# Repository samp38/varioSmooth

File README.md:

# VarioSmooth

Lightweight, solar powered, helmet embedded audio variometer for free flight.

- [**v1**](v1/README.md) (2017): PIC24F16KA101 + MS5611, LTC4071 solar charger, 22 × 17 mm PCB. Firmware (MPLAB X / XC16), PCB (Eagle, ported to KiCad 10), docs and open issues.
- [**v2**](v2/README.md) (in progress): nRF52840 (Raytac MDBT50Q) with Bluetooth LE, sends barometric altitude and vario to XCTrack / LK8000. Firmware with PlatformIO, flex PCB.

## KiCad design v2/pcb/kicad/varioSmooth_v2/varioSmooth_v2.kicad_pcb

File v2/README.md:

# VarioSmooth v2 — BLE

Notes de conception pour la modernisation du vario (2026-10).

## Objectifs
- MCU **nRF52840** avec BLE : paramétrage depuis le téléphone + envoi de la pression et du vario à **XCTrack** (puis LK8000) sur Android.
- **Vario sans GPS** : l'application utilise le GPS du téléphone.
- Schéma sous **KiCad**, carte redessinée pour l'intégration dans le casque.
- Firmware compilé/flashé avec **PlatformIO**.
- **Contrainte n°1 : la consommation.**

## Réorientation : deux appareils (2026-10-20, redéfinie le 2026-10-22)
La v1 marche, mais elle est pénible à installer : les fils passés par l'aération cassent, la carte est trop épaisse pour la doublure, et le flashage au PICkit est laborieux. Le projet est scindé en deux appareils :

| | **Vario casque** | **Extension** (cockpit) |
|---|---|---|
| Rôle | Bip + pression et vario (`$LK8EX1`) vers XCTrack : le baro du vario donne une finesse calculée correcte | **Batterie externe** du téléphone + vario (bip activable) + **logger GPS IGC** + BLE |
| Intégration | Dans le casque, cellules solaires sur le dessus, comme la v1 | Boîtier dans le cockpit ou la sellette |
| MCU | nRF52840 (MDBT50Q, ou ISP1807 pour gagner de la place) | nRF52840 |
| USB | **Aucun** : SWD une seule fois, puis OTA BLE | USB-C : recharge, flash, récupération du log |
| Énergie | LiPo + 2 × SP3-12 + LTC4071, comme la v1 | Li-ion **18650** + panneau solaire (prolonge un peu l'autonomie) |
| Interface | Un bouton | Boutons **+ / − / push**, petit écran, menu |

### Vario casque
- **Pas de connecteur USB** (il serait inaccessible) : J1, U1 (protection ESD), R2, R3, R4, D2 et C4 disparaissent. Carte routée avec le MDBT50Q : **20 × 25,25 mm** (~15 × 18 mm estimés avec un ISP1807).
- **Module : à trancher** entre le MDBT50Q et l'**Insight SiP ISP1807** (même nRF52840, donc même firmware) :

  | | MDBT50Q-1MV2 | ISP1807 |
  |---|---|---|
  | Taille | 10,5 × 15,5 × 2,05 mm + zone d'antenne | 8 × 8 × 1 mm, antenne intégrée |
  | Quartz | 32 MHz intégré, 32,768 kHz externe (Y1, C5, C6) | 32 MHz et 32,768 kHz a priori intégrés (à vérifier) |
  | Prix | ~10 € | ~15–20 € (stock à vérifier) |
  | Soudure | Pads accessibles, air chaud possible | LGA à pas fin : pochoir + four |
  | Bootloader | Déjà présent sur un module récupéré d'une Feather | Rien : sonde SWD obligatoire |
  | Carte Adafruit | Définition Feather nRF52840 utilisable telle quelle | Pas de variante : définition de carte à adapter |

  Dans les deux cas, l'antenne doit être au bord de la carte, avec une zone sans cuivre.
- **Flash** : bootloader Adafruit flashé une fois par SWD (sonde CMSIS-DAP), puis mises à jour en **OTA BLE** (nRF Connect ou Bluefruit). Le bouton reste sur **P1.02** : maintenu à la mise sous tension, il lance le bootloader en mode DFU, ce qui permet de récupérer un firmware planté sans ouvrir le casque.
- **Pastilles de test** au dos (Ø 1,5 mm, pas de 2,54 mm, pour pogo pins) : 3V3, GND, RESET, SWDIO, SWDCLK.
- **Reset sans bouton** : la batterie est soudée, on ne peut pas la débrancher pour relancer le nRF. Les pastilles RESET et GND sont voisines : les toucher ensemble avec une pince fait un reset. Un bouton, même petit, dépasserait et risquerait des resets intempestifs dans la doublure. Reset avec P1.02 maintenu (ou double reset) → DFU, pour reflasher une appli plantée ou une OTA ratée. Un bootloader corrompu ne se répare que par SWD.
- **Buzzer sur la carte** : à tester avant de l'adopter. Un piézo CMS (~9 × 9 mm, résonance ~4 kHz) est bien plus faible qu'un KPEG006 aux fréquences du vario (400–1500 Hz) ; il ne convient que si la carte est près de l'oreille. Essai : Feather + piézo CMS contre KPEG006, casque sur la tête, avec un ventilateur.
- **Fils vers les cellules** : point faible de la v1, prévoir un passage propre et un serre-câble collé sur la carte.
- La version avec USB-C (20 × 32,75 mm, commit `d064723`) reste disponible dans l'historique git comme **prototype de développement**.

### Extension : batterie externe, vario et logger
- **Batterie** : 18650 en **1S** (1 ou 2 cellules en parallèle, ~3000–3500 mAh chacune) : pas d'équilibrage, chargeurs et élévateurs courants. 2 cellules : ~37 × 65 × 19 mm, ~95 g. Cellules de marque (Samsung 35E, Molicel, LG).
- **Alimentation** : chargeur type **TI BQ25895** (le LTC4071 ne convient plus) :
  - power path (l'appareil fonctionne pendant la charge) ;
  - sortie 5 V élevée (OTG, ~2–3 A) pour le téléphone ;
  - NTC avec seuils JEITA : pas de charge sous 0 °C ;
  - régulation de la tension d'entrée (VINDPM), qui fait office de MPPT simplifié pour un panneau de 6 V nominal ;
  - suivi par I²C depuis le nRF (niveau, courants, état).
  - Alternative écartée : IP5328P (charge rapide PD/QC intégrée, mais peu documenté et peu pilotable).
- **Connectique** : USB-C en entrée ; sortie USB-C ou USB-A en 5 V seul (le téléphone charge à ~1,5–2 A, suffisant pour XCTrack en vol). La charge rapide PD demanderait un contrôleur USB-PD en plus.
- **Sécurité** : protection de cellule (cellules protégées ou DW01 + MOSFET), fusible, thermistance sur les cellules, boîtier résistant aux chocs.
- **Solaire** : ~1 W en plein soleil → ~150–200 mA dans la batterie, contre 300–600 mA pour un téléphone avec XCTrack. Le panneau alimente l'extension elle-même et ralentit la décharge du téléphone.
- **Écran** : un **Sharp Memory LCD** (ex. LS013B7DH03, 1,28″) plutôt qu'un OLED. Il reste lisible en plein soleil et consomme quelques µA, contre 10–20 mA pour un OLED peu lisible au soleil.
- **Baro** : avec les deux appareils, n'envoyer la pression à XCTrack que depuis l'un des deux (baro désactivable sur l'extension, comme le bip).

### Extension : comportement visé
- Téléphone connecté : trames `$LK8EX1`, bip coupé (XCTrack bipe), sauf si le bip est activé dans le menu.
- Connexion perdue depuis un certain délai : bip automatique.
- Log IGC permanent à 1 Hz (~125 Ko/h, ~130 h sur 16 Mo), récupérable en **USB Mass Storage** (Adafruit_SPIFlash + FatFs + TinyUSB) : le boîtier apparaît comme une clé USB.
- Flash QSPI sur les **mêmes broches que la Feather Express** (P0.17, P0.19–P0.23) : le firmware la gère sans changement, et le logger se prototype sur la Feather (GD25Q16 2 Mo intégrée) avec une carte d'évaluation MAX-M10S.
- Le GNSS consomme 5–30 mW selon la puce (MAX-M10S < 25 mW en suivi), négligeable devant le téléphone. Garder une alimentation de sauvegarde (V_BCKP) pour démarrer à chaud.

## Choix du MCU : module Raytac MDBT50Q (nRF52840)
- **nRF52840 plutôt que nRF52832** (seuls supportés par le core Adafruit) :
  - entrée **VDDH (jusqu'à 5,5 V) + DC/DC intégré** → alimentation directe sur la LiPo, suppression du LDO (ADP160) ;
  - **USB natif** → bootloader UF2, port série de debug (pads D+/D− sur le flex, inutilisés en vol).
- **Module plutôt que chip nu** : antenne, quartz et certification radio inclus, pas de conception RF sur flex.
- **MDBT50Q** = module des Feather nRF52840 → définition de carte et bootloader déjà présents dans le core Adafruit.
- À vérifier dans la datasheet : broches d'alim exposées (VDDH, VBUS, DCCH) et selfs DC/DC intégrées ou non.
- Alternatives : **Insight SiP ISP1807** (~8×8×1 mm, plus cher, LGA, pas de variante Adafruit) ; nRF52840 nu (aQFN73, RF + certification à faire).
- Écarté : nRF54L15 (Zephyr/NCS uniquement, pas de support PlatformIO).

## Framework : PlatformIO + core Arduino Adafruit
- Core Arduino **Adafruit nRF52** : FreeRTOS + SoftDevice S140 (pile BLE Nordic), lib **Bluefruit**, bootloader UF2 + DFU OTA BLE.
- Dans PlatformIO : `platform = nordicnrf52`, `framework = arduino`, `board = adafruit_feather_nrf52840`.
- Autres cores écartés : Arduino Mbed OS (Mbed en fin de vie), forks Seeed.
- **Zephyr écarté** : gain estimé ~10–50 µA en vol sur 0,3–1+ mA (1–5 %), nul à l'arrêt. Le support Zephyr de PlatformIO est en retard (et NCS non supporté).
- Pièges conso sous Arduino :
  - USB CDC actif (garde HFCLK, centaines de µA) ;
  - `loop()` qui tourne sans dormir ;
  - tick FreeRTOS 1024 Hz ;
  - périphériques non coupés ;
  - LED bleue de connexion → `Bluefruit.autoConnLed(false)`.

## Budget conso estimé (en vol, non mesuré)
| Poste | Estimation |
|---|---|
| Capteur MS5611 OSR 4096 @ ~50 Hz (comme la v1) | ~500–700 µA |
| Capteur à fréquence/résolution réduite (ex. 20 Hz) | ~100–300 µA |
| CPU nRF (I2C par DMA, sommeil sinon) | ~20–50 µA |
| BLE connecté (intervalle ~100 ms, trames 4–10 Hz) | ~20–60 µA |
| Buzzer | centaines de µA à quelques mA quand il bipe |
| Plancher repos Zephyr / Arduino | ~2–4 µA / ~5–50 µA |
| Arrêt (System OFF) | ~0,5–1 µA (identique) |

→ Dans la v1, le **capteur** dominait (~0,6 mA sur 1 mA). Les leviers principaux : fréquence/résolution capteur (ou BMP581), buzzer, paramètres BLE.

## Liaison BLE avec XCTrack et LK8000 (Android)
Trame retenue : **`$LK8EX1,<pression Pa>,99999,<vario cm/s>,<température °C>,<batterie>,*<checksum>`**. L'altitude vaut 99999 quand la pression est fournie (l'application la calcule avec son QNH), batterie 999 = non disponible, sinon tension (< 1000) ou 1000 + pourcentage.

| | XCTrack | LK8000 |
|---|---|---|
| **Nordic UART Service** `6E400001-…` (TX `6E400003-…`) | ✅ | ❌ |
| Port série type HM-10 : service `FFE0`, caractéristique `FFE1` | ❌ | ✅ |
| Environmental Sensing `0x181A` (pression `0x2A6D`, température `0x2A6E`) + Battery `0x180F` | ✅ | ✅ |
| Trame `$LK8EX1` | ✅ | ✅ |

- **Choix pour le prototype : Nordic UART + `$LK8EX1`** pour XCTrack. Le core Adafruit fournit le service (`BLEUart`). La trame transporte le vario calculé par notre filtre ; avec la pression seule (ESS), l'application devrait recalculer le vario, avec plus de retard.
- **Vérifié le 2026-10-18** sur un Galaxy S9 : XCTrack se connecte, et il **affiche le vario de la trame**, alors qu'il ne liste que la pression et la température dans les données du capteur. Test fait avec un vario fixe de +3 m/s, carte immobile (environnement PlatformIO `fake_climb`).
- **LK8000 ensuite** : ajouter le service `FFE0`/`FFE1` en parallèle, avec la même trame. Les deux UUID tiennent dans le paquet d'annonce (le nom va dans la réponse au scan).
- Sources : [page External Devices de XCTrack](https://xctrack.org/External_Devices.html) ; code source de LK8000 (`android/src/org/LK8000/BluetoothGattClientPort.java`, `Common/Source/Android/BluetoothSensor.cpp`), dont le scan filtre sur les UUID annoncés.
- Dans XCTrack : choisir le capteur Bluetooth LE dans les réglages des capteurs externes ; le journal (widget log) montre les trames reçues. Pour un premier test, l'application **nRF Connect** suffit à voir les trames.

## App de paramétrage
- Page **Web Bluetooth** (Chrome Android/desktop) plutôt qu'une app native : rien à publier ni maintenir.
- Commandes texte via le canal série BLE (Nordic UART).

## Firmware (`firmware/`)
Projet PlatformIO, environnement `feather_nrf52840` : `pio run -t upload`, puis `pio device monitor` (sortie de debug sur l'USB).

Sortie de debug choisie à la compilation par `DEBUG_OUTPUT` (`src/debug_out.h`) : 0 = aucune (mesures de consommation, vol), 1 = USB, 2 = **SEGGER RTT** par le SWD (carte casque sans USB). L'environnement `rtt` compile avec RTT ; lecture avec une sonde CMSIS-DAP : `probe-rs attach --chip nRF52840_xxAA .pio/build/rtt/firmware.elf`. Le tampon RTT ne bloque pas : sans sonde, les messages en trop sont perdus et le firmware continue. Une sonde branchée consomme ~1 mA.

| Fichier | Rôle |
|---|---|
| `src/ms5611.*` | Pilote du capteur : PROM + CRC4, compensation de température du 2e ordre (absentes en v1). Pression en OSR 4096, température en OSR 1024 (512 en v1). |
| `src/vario.*` | Algorithme de la v1 : filtre passe-bas d'ordre 2 sur la pression, dérivée sur une fenêtre de 10 à 50 échantillons selon la vitesse, filtre IIR sur la vitesse. Calcul en flottant et sur l'altitude (cm/s) plutôt que sur la pression. |
| `src/ble_link.*` | Nordic UART + trames `$LK8EX1`. |
| `src/debug_out.*` | Sortie de debug `dbg` (USB ou RTT), voir `DEBUG_OUTPUT`. |
| `src/audio.*` | Bips de la v1 (tables `beepLen` / `audioFreq`, ton à 2/3, silence en descente) et mélodies (démarrage, volume, arrêt). 3 volumes comme en v1 : boost = deux broches en opposition de phase (le comparateur de la v1 fournissait le signal inversé), high = une seule broche, medium = une 3ᵉ broche à travers une résistance (le potentiomètre numérique de la v1). Réduire le rapport cyclique ne marche pas : le son vient surtout des harmoniques, et chaque front fait sonner le piézo pareil ; il faut arrondir les fronts (RC avec la capacité du piézo). |
| `src/button.*` | Bouton scruté à chaque échantillon (anti-rebond par la période de 20 ms). Appui court : volume suivant (enregistré en flash à l'extinction seulement : une écriture bloque ~0,5 s, le capteur refroidit pendant la pause et le vario voit une fausse montée). Appui long (> 0,5 s) : arrêt en System OFF, le bouton rallume la carte. |
| `src/main.cpp` | Boucle à 50 Hz, même séquence que la v1 : lecture de la pression, conversion courte de la température, lancement de la pression suivante. Trame BLE à 10 Hz. La température doit être fraîche à chaque échantillon : la pression brute dérive d'environ 2 mbar/°C (coefficients typiques), et une température en retard se voit comme une fausse vitesse verticale. |

À venir : arrêt automatique, mesure batterie, réglages de consommation.

### Câblage du prototype (Feather nRF52840 Express)
| Breakout MS5611 (GY-63…) | Feather |
|---|---|
| VCC | 3V |
| GND | GND |
| SCL / SDA | SCL / SDA |
| PS | VCC (mode I2C, souvent déjà fait sur la carte) |
| CSB | GND → adresse 0x77 (VCC → 0x76, détectée aussi) |

Piézo (KPEG006, comme en v1), polarité indifférente :
```
A0 ──[ 220 Ω ]──┬── KPEG006 ── A1
A2 ──[ ~1 kΩ ]──┘   (volume medium, valeur à ajuster à l'oreille)
```
La 220 Ω limite les pics de courant à chaque front (bruit sur le 3,3 V).

## Bloc d'alimentation du vario casque (config v1, retenue le 2026-10-21)

```
SP3-12 ─ SP3-12 ── D1 (Schottky) ── RIN (200 Ω) ──┬── VCC ── VDDH (MDBT50Q) ── REG0 DC/DC ── VDD 3,0 V ── MS5611, buzzer
   (série, côte à côte sur le dessus)               │
                                      LTC4071 (shunt)── BAT ── LiPo (hors carte, pastilles BT1)
```

**Retenu le 2026-10-21 : la configuration de la v1**, qui a toujours fonctionné. Elle remplace les réglages étudiés le 2026-10-17 (RIN 0 Ω, LBSEL à VCC, NTC sur la batterie), conservés ci-dessous pour mémoire :
- **RIN = 200 Ω** ;
- **ADJ en l'air** (fin de charge 4,1 V) ;
- **NTC relié à VCC** : pas de réduction de la tension de fin de charge à chaud ;
- **LBSEL à GND** : coupure à 3,2 V, meilleure conservation pendant les longs mois sans vol.

**Froid** : d'après la datasheet, le NTC du LTC4071 ne fait que baisser la tension de fin de charge au-dessus de 40 °C. Il n'y a **aucune coupure de charge par temps froid**. Le courant de charge est minuscule, mais charger une LiPo sous 0 °C reste un risque. Parade possible : un P-MOSFET entre les cellules et le LTC4071, coupé par le nRF sous 0 °C (température du MS5611).

### Chargeur : LTC4071 (shunt, MSOP8 ou DFN 2 × 3 mm), comme la v1
Le **BQ25505** (MPPT) a été envisagé puis écarté. Les cellules sont côte à côte sur le dessus du casque, donc à l'ombre ensemble : la série ne pénalise pas. Et avec RIN ≈ 0, le LTC4071 récupère déjà ~75 % de la puissance des cellules, contre ~80–85 % pour le BQ25505 (estimations, non mesurées). Ce faible gain ne justifiait pas :
- l'abandon de la **coupure batterie basse intégrée** (le BQ25505 descend à 1,95 V et impose une batterie avec PCM) ;
- l'abandon de la **réduction de la tension de fin de charge à chaud** (NTC) ;
- l'ajout d'une self, d'un convertisseur à découpage à côté du capteur et de la radio, et de 8 résistances de 1 à 14 MΩ.

Principe : les cellules débitent dans VCC (la charge système). Le LTC4071 dérive l'excédent (jusqu'à 50 mA) pour maintenir VCC à la tension de fin de charge, et relie la batterie à VCC par un interrupteur interne (4–6 Ω). Iq : 550 nA typ. (1,2 µA max). Fuite batterie une fois déconnectée : < 0,1 nA typ.

| Réglage | Choix | Effet |
|---|---|---|
| **RIN** | **0 Ω** (empreinte gardée) | La datasheet n'exige RIN que si la source peut dépasser 50 mA de shunt. Isc des SP3-12 : 10,7 mA. En v1, 220 Ω coûtaient ~15 % de la récolte en plein soleil (~64 % contre ~75 %), et presque rien à faible éclairage (pertes en I²). Shunt max avec RIN = 0 : 4,1 V × 11 mA ≈ 45 mW, sans souci. |
| **ADJ** | en l'air | Fin de charge **4,1 V** (4,0 V à GND, 4,2 V à VCC). |
| **NTC / NTCBIAS** | thermistance **10 kΩ « curve 2 »** (B25/85 = 3490, ex. Vishay NTHS0402N02N1002F) de NTC à GND, **collée à la batterie** ; RNOM 10 kΩ de NTCBIAS à NTC | Avec ADJ en l'air : 4,1 V < 40 °C, puis 4,025 / 3,95 / 3,875 / 3,8 V par paliers de 10 °C. Sur un casque au soleil, c'est le principal levier de durée de vie de la LiPo. Polarisation pulsée : ~50 pA en moyenne. |
| **LBSEL** | **à VCC** | Coupure batterie à **2,7 V**, reconnexion quand VCC atteint 3,6 V. Voir la remarque ci-dessous. |
| **HBO** | non connecté | Sortie CMOS au niveau de VCC (jusqu'à 4,1 V), au-delà de ce que tolère une GPIO du nRF (3,3 V). La batterie se mesure par le SAADC. |
| **D1** | Schottky à **faible courant inverse** | Anti-retour : sans elle, les cellules déchargent la batterie la nuit (recommandé par la datasheet). Choisir sur le courant inverse sous 4 V (il augmente fortement avec la température), plus que sur le Vf. |
| **CVCC** | 10 µF (+ les 10 µF de VDDH) | Absorbe les pics d'émission BLE à travers les 4–6 Ω de l'interrupteur batterie. |

**Pourquoi LBSEL à VCC (2,7 V) et pas à GND (3,2 V) comme en v1** : après une coupure, la batterie n'est reconnectée que quand VCC atteint VLBC_VCC. Avec LBSEL à GND, ce seuil vaut **4,19 V typ.** (à 1 mA), soit **au-dessus** de la tension de fin de charge de 4,1 V (ADJ en l'air) à laquelle le shunt plafonne VCC. La reconnexion ne se fait alors qu'à faible courant de charge, où le seuil baisse : c'est **limite**. Avec LBSEL à VCC, le seuil tombe à 3,6 V, sans ambiguïté. La coupure à 2,7 V est profonde pour une LiPo : c'est un **dernier recours**, et le firmware s'arrête bien avant (voir « Gestion de l'énergie »).

### Cellules solaires
- 2 × SP3-12 **en série**, comme en v1 : Vmp ~6 V, Voc ~9 V (jusqu'à ~10 V à froid, sans conséquence pour un shunt), Isc ~10,7 mA, ~50 mW en plein soleil.
- La charge démarre dès que la tension de la chaîne dépasse Vbat + Vf de D1 (~4,2–4,5 V). Le Voc du silicium amorphe chute peu à faible éclairage, donc la charge fonctionne même par temps couvert, avec un courant proportionnel à la lumière.

### MDBT50Q (nRF52840), alimentation
- Dimensions : 10,5 × 15,5 × 2,05 mm. Le quartz 32 MHz et la self du DC/DC REG1 sont **intégrés**.
- Schéma de référence « Reg0 DC/DC Enabled » (VDDH ≥ 3,6 V) :
  - VDDH (broche 30) ← VCC du LTC4071, 10 µF (VDDH accepte 2,5–5,5 V, VCC ne dépasse pas 4,1 V) ;
  - DCCH (31) → **L 10 µH 0603 (≥ 80 mA)** → VDD (28), 10 µF ;
  - VBUS (32) relié à GND, D+/D− (35/34) non connectés : pas d'USB (flash par SWD puis OTA BLE).
  - P0.18 en broche de reset (pastille RESET), configuré par le bootloader Adafruit.
- **VDD = REGOUT0 réglé à 3,0 V** (registre UICR) plutôt que 3,3 V : le régulateur reste en régulation jusqu'à une batterie à ~3,3 V (le seuil d'arrêt du firmware), et le MS5611 accepte 1,8–3,6 V. À prévoir dans la définition de carte et le bootloader (la valeur par défaut est 1,8 V).
- **Quartz 32,768 kHz** (optionnel selon Raytac) : **retenu**. Il évite l'oscillateur RC, qui se recalibre périodiquement et impose des fenêtres de réception BLE plus larges (500 ppm), donc plus de temps radio.
- Mesure de la batterie : canal **VDDHDIV5** interne du SAADC → pas de pont diviseur externe (trame `$LK8EX1` + service Battery).

### Gestion de l'énergie
- Le firmware mesure la batterie par le SAADC (VDDHDIV5). Sous **~3,4 V**, il passe en **veille « batterie faible »** : tout est coupé (capteur, buzzer, BLE), et le nRF reste en System ON avec un réveil RTC toutes les minutes environ pour remesurer. Il redémarre au-dessus de **~3,7 V**, après une recharge solaire.
- Pas de System OFF dans ce cas : aucun signal externe ne pourrait réveiller le nRF quand la batterie remonte, puisque HBO ne monte qu'à pleine charge et dépasse le niveau toléré par les GPIO.
- Consommation estimée en veille batterie faible : nRF en System ON + RTC ~1,5–3 µA + LTC4071 0,55 µA + MS5611 en veille < 0,15 µA → **~2–4 µA**. Avec une LiPo de 40 mAh arrêtée à 3,4 V (~10 % restants), il reste plusieurs semaines avant la coupure matérielle.
- Dernier recours : le LTC4071 déconnecte la batterie à 2,7 V (fuite < 0,1 nA ensuite) et la reconnecte dès que les cellules ramènent VCC à 3,6 V. Une PCM dans la batterie n'est pas indispensable, mais elle ne gêne pas.

## Autres pistes hardware
- **Buzzer** : PWM du nRF avec 2 canaux en opposition = pont en H natif (plus de comparateur ni de MCP4542) ; volume par rapport cyclique.
- **Récupération solaire** : LTC4071 conservé, voir « Bloc d'alimentation ».
  - Cellules conservées : **2 × PowerFilm SP3-12** (silicium amorphe souple, 12,7 × 64 mm), côte à côte sur le dessus du casque. Par cellule, en plein soleil : Vmp 3,0 V / Imp 8,5 mA (~25 mW), Voc 4,5 V, Isc 10,7 mA.
  - Bilan grossier : 50 mW en plein soleil, ~5–15 mW réalistes sur le casque → ~1–3 mA de charge, contre 0,3–1 mA consommés en vol.
  - Option écartée : récupérateur MPPT (TI BQ25505, e-peas AEM10941) avec les cellules en parallèle. Il ne vaut le coup que si les cellules sont souvent ombrées différemment. L'AEM10941 est de toute façon limité à un Voc de 5,0 V, trop juste pour 2 SP3-12 en parallèle par temps froid.
- **Batterie** (vario casque) : petite LiPo souple 40–100 mAh au lieu de la LIR2016 (~20 mAh), hors carte, reliée aux pastilles BT1. Modèle à choisir.
- **Capteur** : **MS5611 retenu** (connu, même algorithme que la v1). Levier conso : OSR et fréquence d'échantillonnage. BMP581 écarté pour l'instant. Accéléromètre en option (fusion Kalman), coûteux en conso.
- **PCB souple** : raidisseurs sous module/capteur ; capteur protégé du vent (mousse) ; antenne orientée vers l'extérieur, zone dégagée respectée.

## Mesure de consommation
### Outil : PPK2 (Nordic Power Profiler Kit II, ~100 €)
Pas indispensable, mais fortement recommandé. Un multimètre lisse mal les pics (µA → 10 mA en quelques µs), et sa chute de tension en calibre µA fait redémarrer le nRF.
- Mesure 200 nA → 1 A, calibre automatique, 100 kéch/s.
- Alimentation réglable 0,8–5 V (mode source) ou ampèremètre en série.
- 8 entrées logiques synchronisées avec la courbe.
- Moyenne sur fenêtre (nRF Connect Power Profiler).
- Alternatives : multimètre (états stables seulement), CurrentRanger (+ oscillo), Joulescope / Otii Arc (5–10× plus chers), décharge batterie (lent).

### Montage sur la Feather nRF52840 Express
| Parasite | Impact | Action |
|---|---|---|
| NeoPixel | ~0,5–1 mA permanent | dessouder / couper l'alim |
| LDO AP2112 | dizaines de µA | **EN → GND** |
| Pont diviseur VBAT (100k/100k) | ~20 µA | pas de batterie |
| Chargeur MCP73831 | négligeable | pas d'USB |
| Flash QSPI | quelques µA | veille profonde (cmd `0xB9`) |
| LED rouge / bleue | si allumées | `Bluefruit.autoConnLed(false)` |

1. PPK2 en mode source **3,3 V sur la broche 3V** + GND, sans USB ni batterie.
2. Entrées logiques du PPK2 sur des GPIO de repère (capteur, I2C, BLE, bip).
3. Vérifier **VBAT ≈ 0 V** (sinon retour de courant par le LDO).
4. **Firmware « plancher »** : flash en veille profonde + `sd_power_system_off()` → attendu ~0,5 µA. Quelques µA = OK (à soustraire) ; des dizaines ou centaines = parasite restant.
- Capteur : sur les cartes du commerce (ex. GY-63), contourner le régulateur et mesurer séparément. Pull-ups I2C 10 kΩ = 330 µA par ligne tant qu'elle est à l'état bas.
- Limites : la Feather alimente le nRF en 3,3 V, alors que la carte finale l'alimentera directement par la LiPo via VDDH (chiffres proches mais pas identiques). Option propre : **nRF52840 DK** (~50 €), qui a un point de mesure prévu pour le PPK2.

## Plan
1. ~~**Prototype** : Feather nRF52840 + carte capteur, PlatformIO/Adafruit, liaison XCTrack~~ (fait) ; LK8000 et mesures au PPK2 à venir.
2. **Vario casque** :
   - carte compacte `pcb/kicad/varioSmooth_v2` routée (sans USB, 20 × 25,25 mm), à fabriquer et valider : flash SWD, puis OTA BLE ;
   - test du buzzer CMS.
3. **Extension** :
   - logger IGC prototypé sur la Feather (flash QSPI intégrée + carte d'évaluation MAX-M10S) ;
   - nouveau schéma : 18650 + BQ25895, GNSS, flash, écran, 3 boutons ;
   - boîtier pour le cockpit, PCB rigide.

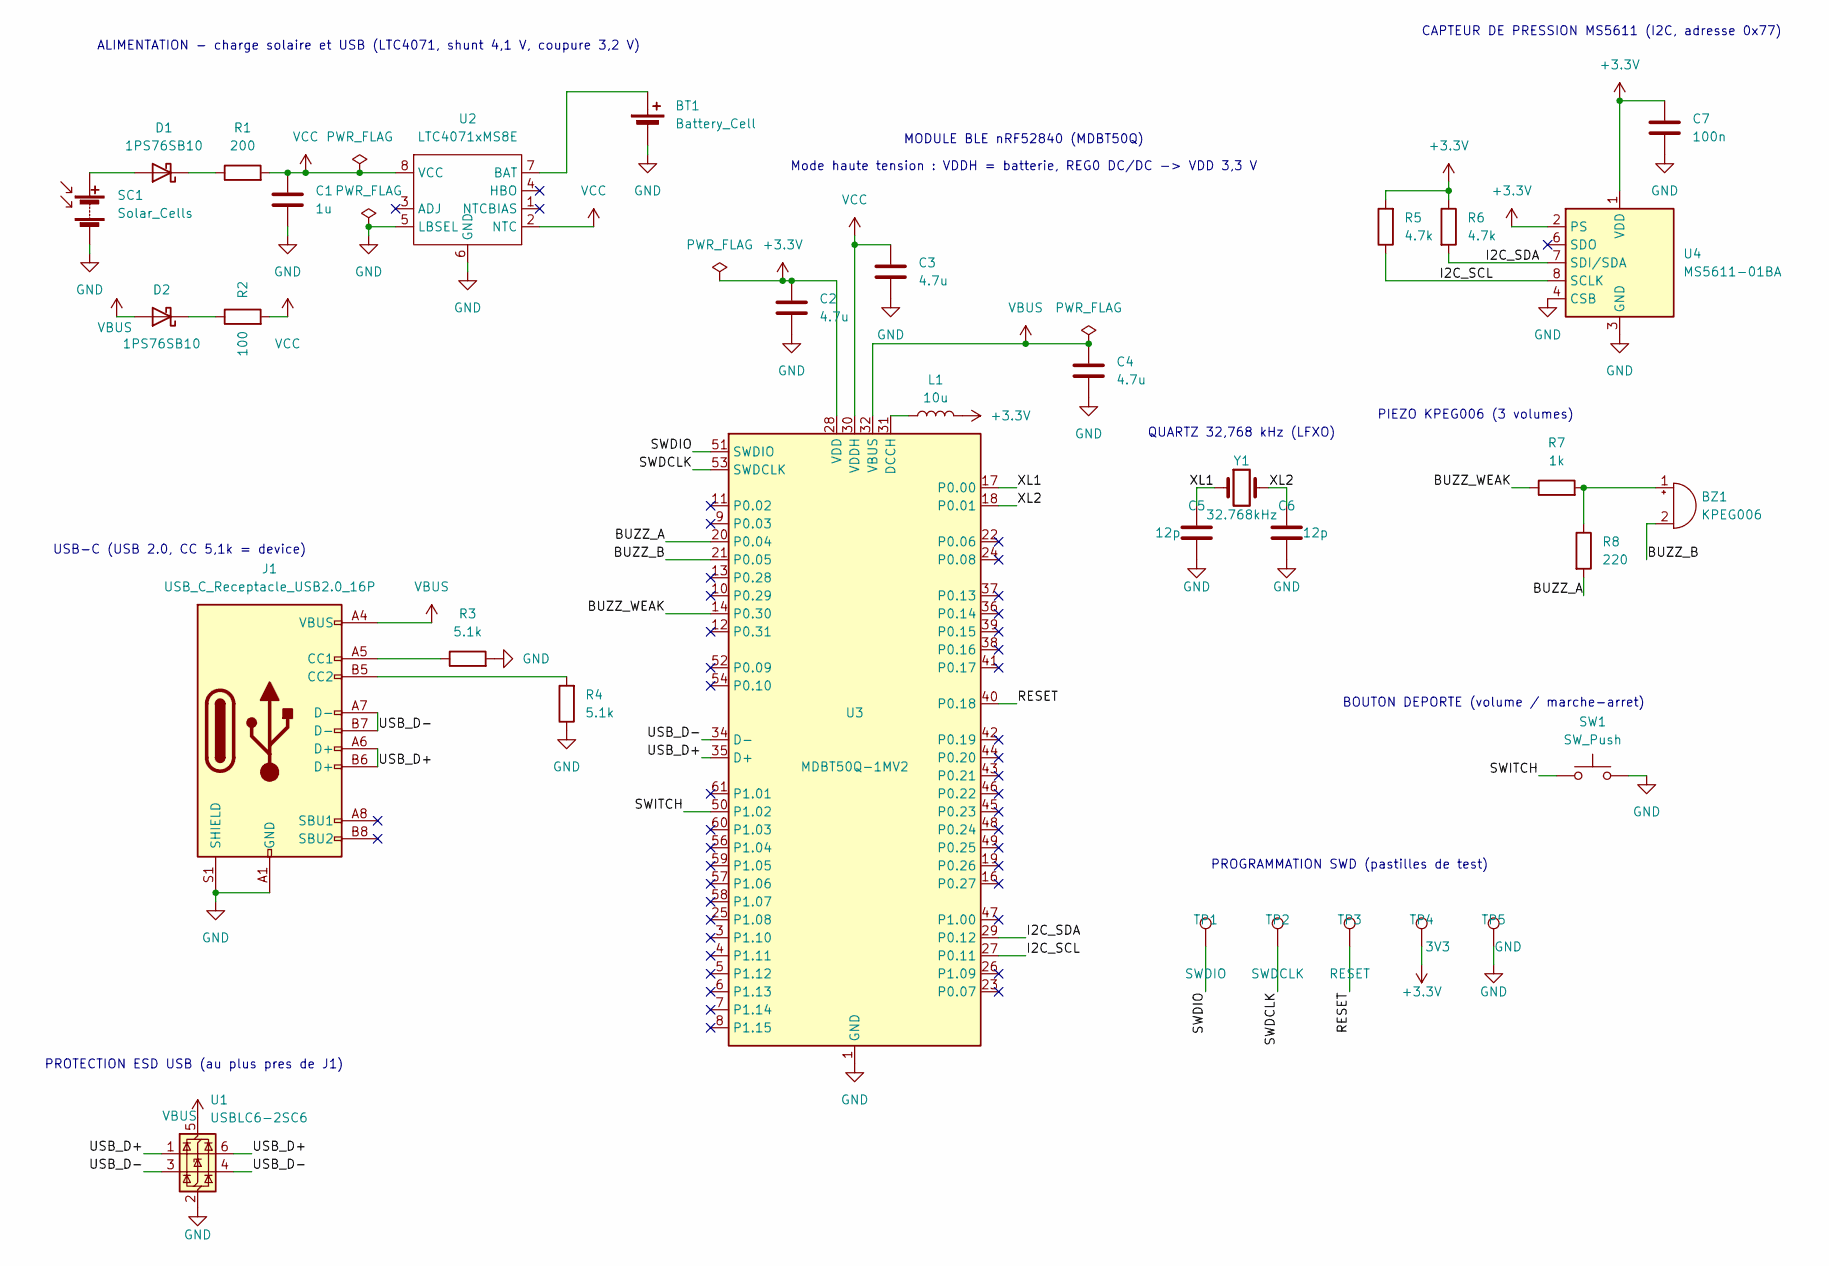
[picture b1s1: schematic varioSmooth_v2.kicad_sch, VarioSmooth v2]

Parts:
BT1: Battery_Cell; WirePad_1x02_SMD_P2.54mm
BZ1: KPEG006; WirePad_1x02_SMD_P2.54mm
C1: 1u; C_0603_1608Metric; LCSC C15849
C2, C3, C4: 4.7u; C_0603_1608Metric; LCSC C19666
C5, C6: 12p; C_0603_1608Metric; LCSC C38523
C7: 100n; C_0603_1608Metric; LCSC C14663
D1, D2: 1PS76SB10; D_SOD-323; LCSC C551397
J1: USB_C_Receptacle_USB2.0_16P; USB_C_Receptacle_GCT_USB4105-xx-A_16P_TopMnt_Horizontal; LCSC C3020560
L1: 10u; L_0603_1608Metric; MPN LQM18DN100M70L; LCSC C713281
R1: 200; R_0603_1608Metric; LCSC C8218
R2: 100; R_0603_1608Metric; LCSC C22775
R3, R4: 5.1k; R_0603_1608Metric; LCSC C23186
R5, R6: 4.7k; R_0603_1608Metric; LCSC C23162
R7: 1k; R_0603_1608Metric; LCSC C21190
R8: 220; R_0603_1608Metric; LCSC C22962
SC1: Solar_Cells; WirePad_1x02_SMD_P2.54mm
SW1: SW_Push; WirePad_1x02_SMD_P2.54mm
TP1: SWDIO; TestPoint_Pad_D1.5mm
TP2: SWDCLK; TestPoint_Pad_D1.5mm
TP3: RESET; TestPoint_Pad_D1.5mm
TP4: 3V3; TestPoint_Pad_D1.5mm
TP5: GND; TestPoint_Pad_D1.5mm
U1: USBLC6-2SC6; SOT-23-6; LCSC C7519
U2: LTC4071xMS8E; MSOP-8-1EP_3x3mm_P0.65mm_EP1.68x1.88mm
U3: MDBT50Q-1MV2; Raytac_MDBT50Q; LCSC C5118826
U4: MS5611-01BA; LGA-8_3x5mm_P1.25mm; LCSC C37148
Y1: 32.768kHz; Crystal_SMD_3215-2Pin_3.2x1.5mm; LCSC C99010

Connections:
+3.3V: C2.1, C7.1, L1.2, R5.2, R6.1, TP4.1 (1_1), U3.28 (VDD), U4.1 (VDD), U4.2 (PS)
/BUZZ_A: R8.2, U3.20 (P0.04)
/BUZZ_B: BZ1.2 (-), U3.21 (P0.05)
/BUZZ_WEAK: R7.1, U3.14 (P0.30)
/I2C_SCL: R5.1, U3.27 (P0.11), U4.8 (SCLK)
/I2C_SDA: R6.2, U3.29 (P0.12), U4.7 (SDI/SDA)
/RESET: TP3.1 (1_1), U3.40 (P0.18)
/SWDCLK: TP2.1 (1_1), U3.53 (SWDCLK)
/SWDIO: TP1.1 (1_1), U3.51 (SWDIO)
/SWITCH: SW1.1, U3.50 (P1.02)
/USB_D+: J1.A6 (D+), J1.B6 (D+), U1.1 (I/O1), U1.6 (I/O1), U3.35 (D+)
/USB_D-: J1.A7 (D-), J1.B7 (D-), U1.3 (I/O2), U1.4 (I/O2), U3.34 (D-)
/XL1: C5.1, U3.17 (P0.00), Y1.1
/XL2: C6.1, U3.18 (P0.01), Y1.2
GND: BT1.2 (-), C1.2, C2.2, C3.2, C4.2, C5.2, C6.2, C7.2, J1.A1 (GND), J1.A12 (GND), J1.B1 (GND), J1.B12 (GND), J1.S1 (SHIELD), R3.2, R4.1, SC1.2 (-), SW1.2, TP5.1 (1_1), U1.2 (GND), U2.5 (LBSEL), U2.6 (GND), U2.9 (GND), U3.1 (GND), U3.2 (GND), U3.15 (GND), U3.33 (GND), U3.55 (GND), U4.3 (GND), U4.4 (CSB), U4.5 (CSB)
unnamed: BT1.1 (+), U2.7 (BAT)
unnamed: BZ1.1 (+), R7.2, R8.1
unnamed: D1.2 (A), SC1.1 (+)
unnamed: D1.1 (K), R1.1
unnamed: D2.1 (K), R2.1
unnamed: J1.A5 (CC1), R3.1
unnamed: J1.B5 (CC2), R4.2
unnamed: L1.1, U3.31 (DCCH)
VBUS: C4.1, D2.2 (A), J1.A4 (VBUS), J1.A9 (VBUS), J1.B4 (VBUS), J1.B9 (VBUS), U1.5 (VBUS), U3.32 (VBUS)
VCC: C1.1, C3.1, R1.2, R2.2, U2.2 (NTC), U2.8 (VCC), U3.30 (VDDH)

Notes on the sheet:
PROTECTION ESD USB (au plus pres de J1)
Mode haute tension : VDDH = batterie, REG0 DC/DC -> VDD 3,3 V
MODULE BLE nRF52840 (MDBT50Q)
QUARTZ 32,768 kHz (LFXO)
BOUTON DEPORTE (volume / marche-arret)
ALIMENTATION - charge solaire et USB (LTC4071, shunt 4,1 V, coupure 3,2 V)
CAPTEUR DE PRESSION MS5611 (I2C, adresse 0x77)
USB-C (USB 2.0, CC 5,1k = device)
PROGRAMMATION SWD (pastilles de test)
PIEZO KPEG006 (3 volumes)

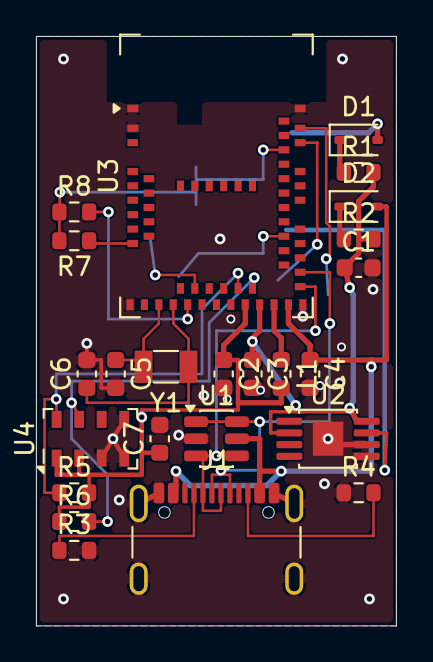
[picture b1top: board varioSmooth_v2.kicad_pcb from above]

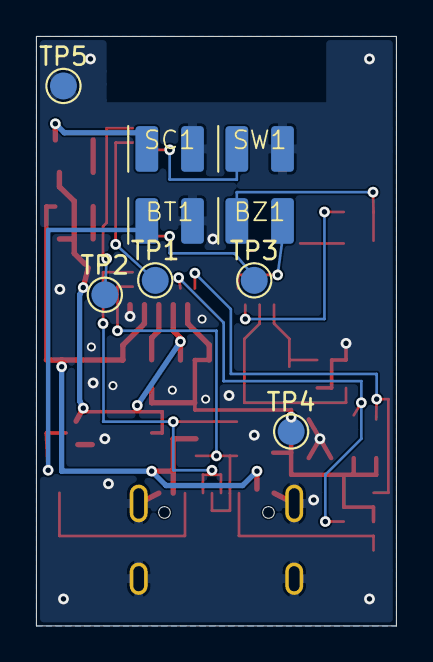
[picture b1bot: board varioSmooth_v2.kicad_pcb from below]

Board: 2 copper layers, 20.0 x 32.8 mm, 33 parts (9 on the bottom side), 25 nets.

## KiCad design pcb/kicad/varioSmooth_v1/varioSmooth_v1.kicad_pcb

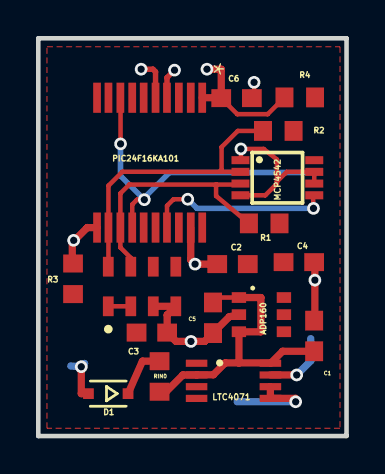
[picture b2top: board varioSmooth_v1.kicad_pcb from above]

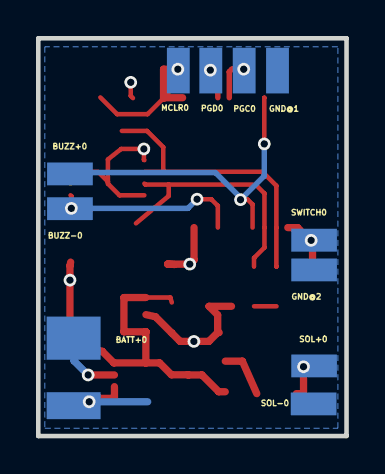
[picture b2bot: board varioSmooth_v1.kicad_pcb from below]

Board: 2 copper layers, 17.1 x 22.1 mm, 28 parts (11 on the bottom side), 14 nets.

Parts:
ADP160: TSOT23-6_DDC
BATT+0: VARIO_LIPO
BUZZ+0: WIREPADSMD1,27-254; SMD1,27-2,54
BUZZ-0: WIREPADSMD1,27-254; SMD1,27-2,54
C1, C4, C5: 1µ; C0603
C2, C3, C6: 100nF; C0603
D1: SOD323-R
GND@1, GND@2: WIREPADSMD1,27-254; SMD1,27-2,54
LTC4071: LTC4071; MSOP8
MCLR0: WIREPADSMD1,27-254; SMD1,27-2,54
MCP4542: MCP4542; MSOP8
MS5611: MS5607PACKAGEDNORMAL; MS5607-02BA03
PGC0: WIREPADSMD1,27-254; SMD1,27-2,54
PGD0: WIREPADSMD1,27-254; SMD1,27-2,54
PIC24F16KA101: SSOP20_MC
R1, R2, R3, R4: 10k; R0603
RIN0: 440; R0603
SOL+0: WIREPADSMD1,27-254; SMD1,27-2,54
SOL-0: WIREPADSMD1,27-254; SMD1,27-2,54
SWITCH0: WIREPADSMD1,27-254; SMD1,27-2,54

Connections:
BATT: BATT+0.P$1, LTC4071.7
BUZZER+: BUZZ+0.1, PIC24F16KA101.8, PIC24F16KA101.14
BUZZER-: BUZZ-0.1, MCP4542.5, PIC24F16KA101.17
GND: ADP160.2, BATT+0.P$2, C1.2, C2.2, C3.1, C4.2, C5.2, C6.1, GND@1.1, GND@2.1, LTC4071.5, LTC4071.6, MCP4542.1, MCP4542.4, MCP4542.6, MCP4542.7, MS5611.3, MS5611.4, PIC24F16KA101.19, SOL-0.1
MCLR: C6.2, MCLR0.1, PIC24F16KA101.1, R4.1
unnamed: D1.C, RIN0.1
PGC: PGC0.1, PIC24F16KA101.5
PGD: PGD0.1, PIC24F16KA101.4
SCL: MCP4542.2, MS5611.8, PIC24F16KA101.12, R2.1
SDA: MCP4542.3, MS5611.7, PIC24F16KA101.13, R1.1
SOL+: D1.A, SOL+0.1
SWITCH_WIRE: PIC24F16KA101.11, R3.1, SWITCH0.1
SYS_LOAD: ADP160.6, C2.1, C3.2, C4.1, MCP4542.8, MS5611.1, MS5611.2, PIC24F16KA101.20, R1.2, R2.2, R3.2, R4.2
TO_REGULATOR: ADP160.1, ADP160.3, C1.1, C5.1, LTC4071.2, LTC4071.8, RIN0.2

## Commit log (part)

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2017-09-06 remove old backup files
2018-06-04 Doc
    Doc
2018-06-05 gitignore
